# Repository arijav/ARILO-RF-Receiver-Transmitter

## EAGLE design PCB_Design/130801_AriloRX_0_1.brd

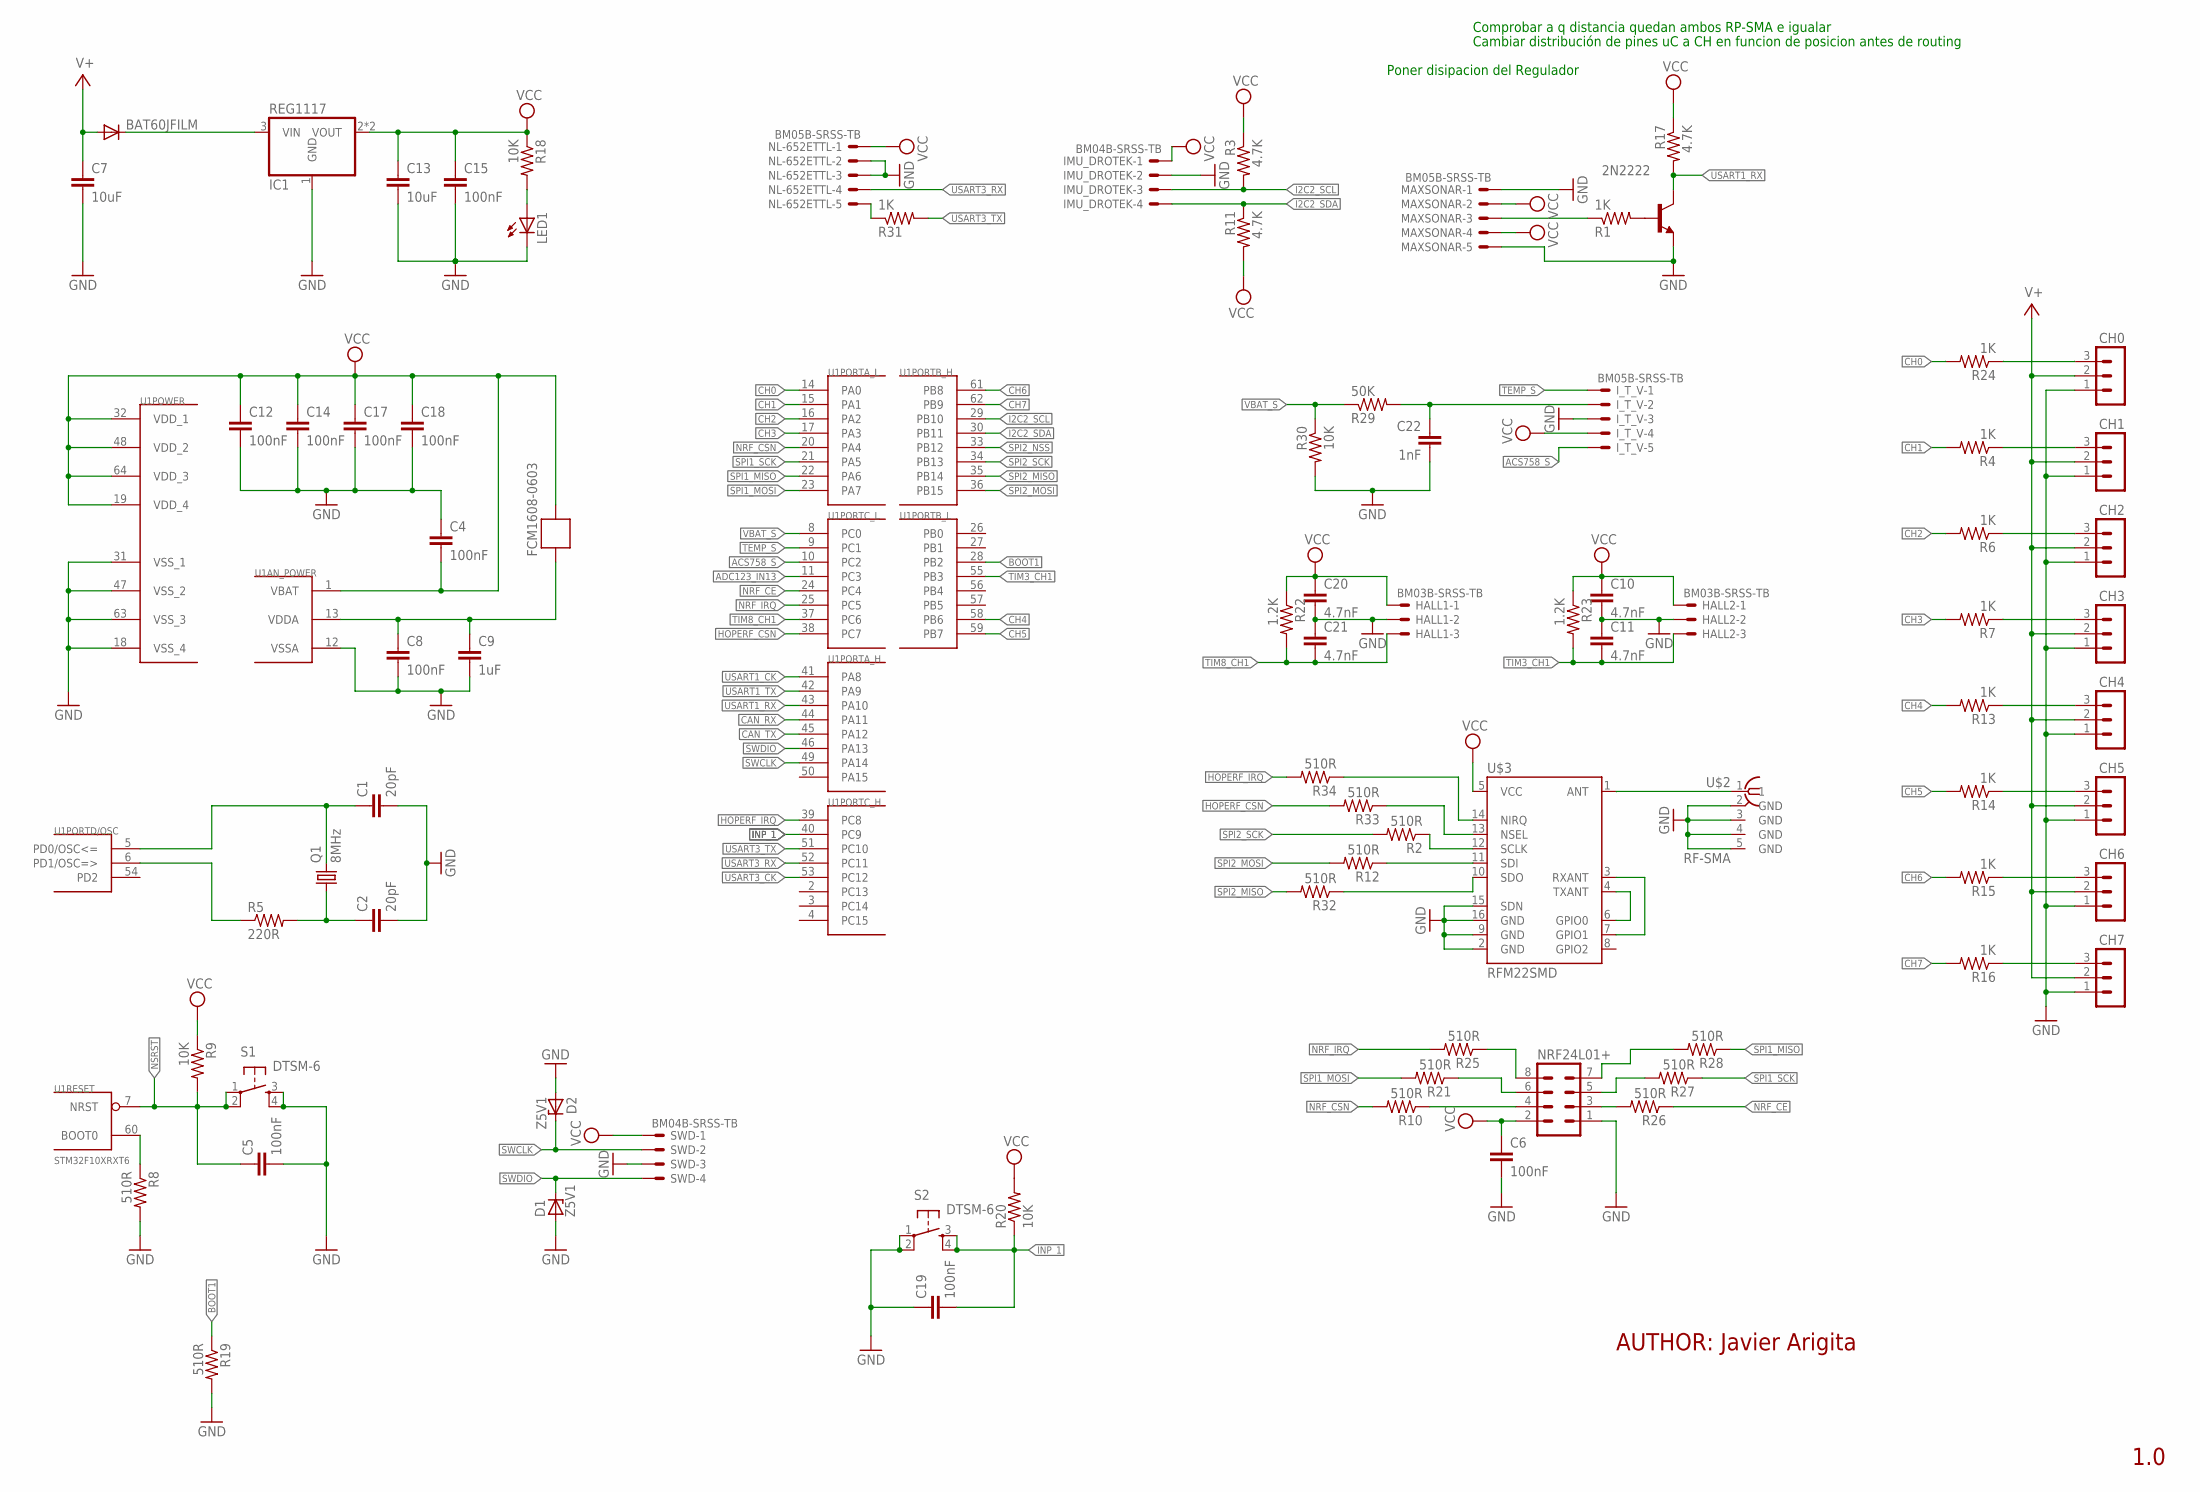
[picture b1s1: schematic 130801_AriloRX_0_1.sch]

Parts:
2N2222: MMBT2222ALT1-NPN-SOT23-BEC; SOT23-BEC
BAT60JFILM: DIODE-SOD323-R; SOD323-R
C1, C2: 20pF; C0805
C4, C5, C6, C8, C12, C14, C15, C17, C18, C19: 100nF; C0805
C7, C13: 10uF; C3216
C9: 1uF; C3216
C10, C11, C20, C21: 4.7nF; C0805
C22: 1nF; C0805
CH0, CH1, CH2, CH3, CH4, CH5, CH6, CH7: MA03-1
D1, D2: Z5V1; SOD80C
FCM1608-0603: FERRITE-BEAD; R0603
HALL1, HALL2: BM03B-SRSS-TB
IC1: REG1117; SOT223
IMU_DROTEK: BM04B-SRSS-TB
I_T_V: BM05B-SRSS-TB
LED1: LED0805; CHIPLED_0805
MAXSONAR: BM05B-SRSS-TB
NL-652ETTL: BM05B-SRSS-TB
NRF24L01+: MA04-2
Q1: 8MHz; SM49
R1, R4, R6, R7, R13, R14, R15, R16, R24, R31: 1K; R0805
R2, R8, R10, R12, R19, R21, R25, R26, R27, R28, R32, R33, R34: 510R; R0805
R3, R11, R17: 4.7K; R0805
R5: 220R; R0805
R9, R18, R20, R30: 10K; R0805
R22, R23: 1.2K; R0805
R29: 50K; R0805
S1, S2: DTSM-6
SWD: BM04B-SRSS-TB
U1: STM32F10XRXT6; TQFP64
U$2: RF-SMA; BU-SMA-H
U$3: RFM22SMD; RFM22-XXX-S2

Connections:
ACS758_S: I_T_V.5, U1.10 (PC2)
ADC123_IN13: U1.11 (PC3)
BOOT1: R19.1, U1.28 (PB2)
CAN_RX: U1.44 (PA11)
CAN_TX: U1.45 (PA12)
CH0: R24.2, U1.14 (PA0)
CH1: R4.2, U1.15 (PA1)
CH2: R6.2, U1.16 (PA2)
CH3: R7.2, U1.17 (PA3)
CH4: R13.2, U1.58 (PB6)
CH5: R14.2, U1.59 (PB7)
CH6: R15.2, U1.61 (PB8)
CH7: R16.2, U1.62 (PB9)
GND: 2N2222.E, C1.2, C2.2, C4.1, C5.2, C6.2, C7.2, C8.2, C9.2, C10.2, C11.1, C12.2, C13.2, C14.2, C15.2, C17.2, C18.2, C19.1, C20.2, C21.1, C22.2, CH0.1, CH1.1, CH2.1, CH3.1, CH4.1, CH5.1, CH6.1, CH7.1, D1.A, D2.A, HALL1.2, HALL2.2, IC1.1 (GND), IMU_DROTEK.2, I_T_V.3, LED1.C, MAXSONAR.1, MAXSONAR.5, NL-652ETTL.2, NL-652ETTL.3, NRF24L01+.1, R8.2, R19.2, R30.2, S1.3, S1.4, S2.1, S2.2, SWD.3, U1.12 (VSSA), U1.18 (VSS_4), U1.31 (VSS_1), U1.47 (VSS_2), U1.63 (VSS_3), U$2.2 (GND), U$2.3 (GND), U$2.4 (GND), U$2.5 (GND), U$3.2 (GND), U$3.9 (GND), U$3.15 (SDN), U$3.16 (GND)
HOPERF_CSN: R33.2, U1.38 (PC7)
HOPERF_IRQ: R34.2, U1.39 (PC8)
I2C2_SCL: IMU_DROTEK.3, R3.2, U1.29 (PB10)
I2C2_SDA: IMU_DROTEK.4, R11.1, U1.30 (PB11)
INP_1: C19.2, R20.1, S2.3, S2.4, U1.40 (PC9)
unnamed: C1.1, Q1.2, U1.5 (PD0/OSC<=)
unnamed: R5.1, U1.6 (PD1/OSC=>)
unnamed: C2.1, Q1.1, R5.2
unnamed: R8.1, U1.60 (BOOT0)
unnamed: U$3.3 (RXANT), U$3.7 (GPIO1)
unnamed: U$3.4 (TXANT), U$3.6 (GPIO0)
unnamed: R2.1, U$3.12 (SCLK)
unnamed: R12.1, U$3.11 (SDI)
unnamed: CH0.3, R24.1
unnamed: LED1.A, R18.2
unnamed: NL-652ETTL.5, R31.1
unnamed: R32.1, U$3.10 (SDO)
unnamed: BAT60JFILM.C, IC1.3 (VIN)
unnamed: MAXSONAR.3, R1.1
unnamed: C22.1, I_T_V.2, R29.2
unnamed: 2N2222.B, R1.2
unnamed: C8.1, C9.1, FCM1608-0603.2, U1.13 (VDDA)
unnamed: NRF24L01+.4, R10.1
unnamed: NRF24L01+.3, R26.2
unnamed: U$2.1, U$3.1 (ANT)
unnamed: CH2.3, R6.1
unnamed: R34.1, U$3.14 (NIRQ)
unnamed: CH4.3, R13.1
unnamed: R33.1, U$3.13 (NSEL)
unnamed: CH3.3, R7.1
unnamed: CH6.3, R15.1
unnamed: CH5.3, R14.1
unnamed: CH7.3, R16.1
unnamed: NRF24L01+.5, R27.2
unnamed: NRF24L01+.6, R21.1
unnamed: NRF24L01+.8, R25.1
unnamed: NRF24L01+.7, R28.2
unnamed: CH1.3, R4.1
NRF_CE: R26.1, U1.24 (PC4)
NRF_CSN: R10.2, U1.20 (PA4)
NRF_IRQ: R25.2, U1.25 (PC5)
NSRST: C5.1, R9.2, S1.1, S1.2, U1.7 (NRST)
SPI1_MISO: R28.1, U1.22 (PA6)
SPI1_MOSI: R21.2, U1.23 (PA7)
SPI1_SCK: R27.1, U1.21 (PA5)
SPI2_MISO: R32.2, U1.35 (PB14)
SPI2_MOSI: R12.2, U1.36 (PB15)
SPI2_NSS: U1.33 (PB12)
SPI2_SCK: R2.2, U1.34 (PB13)
SWCLK: D2.C, SWD.2, U1.49 (PA14)
SWDIO: D1.C, SWD.4, U1.46 (PA13)
TEMP_S: I_T_V.1, U1.9 (PC1)
TIM3_CH1: C11.2, HALL2.3, R23.2, U1.55 (PB3)
TIM8_CH1: C21.2, HALL1.3, R22.2, U1.37 (PC6)
USART1_CK: U1.41 (PA8)
USART1_RX: 2N2222.C, R17.2, U1.43 (PA10)
USART1_TX: U1.42 (PA9)
USART3_CK: U1.53 (PC12)
USART3_RX: NL-652ETTL.4, U1.52 (PC11)
USART3_TX: R31.2, U1.51 (PC10)
V+: BAT60JFILM.A, C7.1, CH0.2, CH1.2, CH2.2, CH3.2, CH4.2, CH5.2, CH6.2, CH7.2
VBAT_S: R29.1, R30.1, U1.8 (PC0)
VCC: C4.2, C6.1, C10.1, C12.1, C13.1, C14.1, C15.1, C17.1, C18.1, C20.1, FCM1608-0603.1, HALL1.1, HALL2.1, IC1.2 (VOUT), IC1.4 (VOUT), IMU_DROTEK.1, I_T_V.4, MAXSONAR.2, MAXSONAR.4, NL-652ETTL.1, NRF24L01+.2, R3.1, R9.1, R11.2, R17.1, R18.1, R20.2, R22.1, R23.1, SWD.1, U1.1 (VBAT), U1.19 (VDD_4), U1.32 (VDD_1), U1.48 (VDD_2), U1.64 (VDD_3), U$3.5 (VCC)

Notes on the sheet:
AUTHOR: Javier Arigita
1.0
Cambiar distribución de pines uC a CH en funcion de posicion antes de routing
Comprobar a q distancia quedan ambos RP-SMA e igualar
Poner disipacion del Regulador

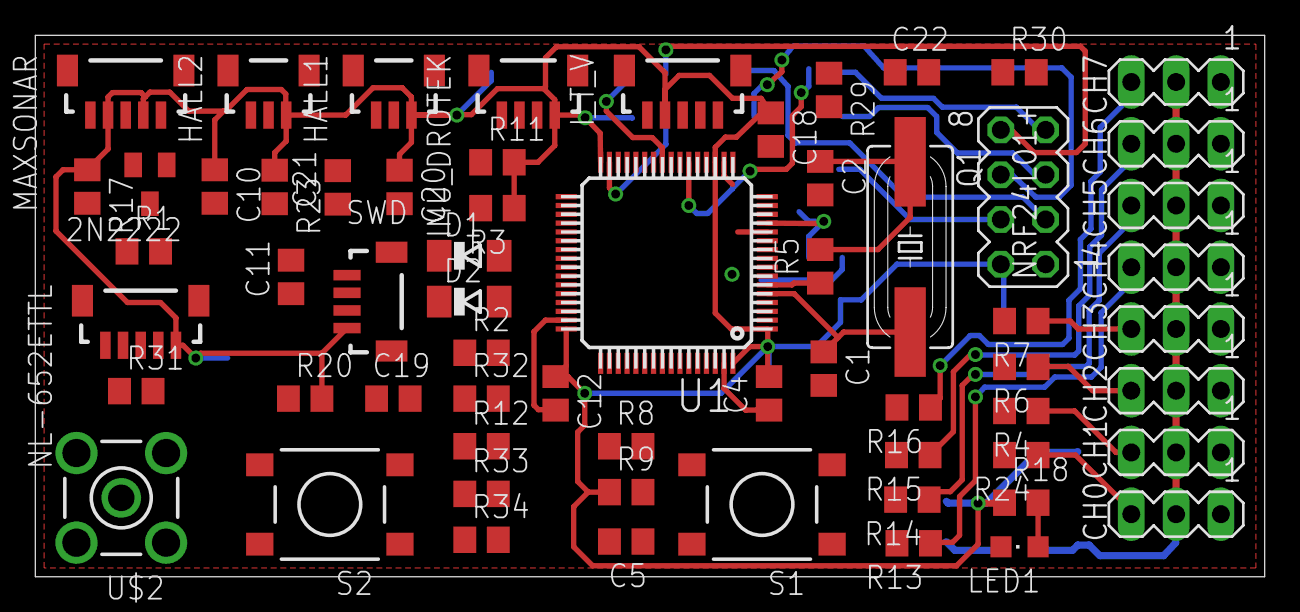
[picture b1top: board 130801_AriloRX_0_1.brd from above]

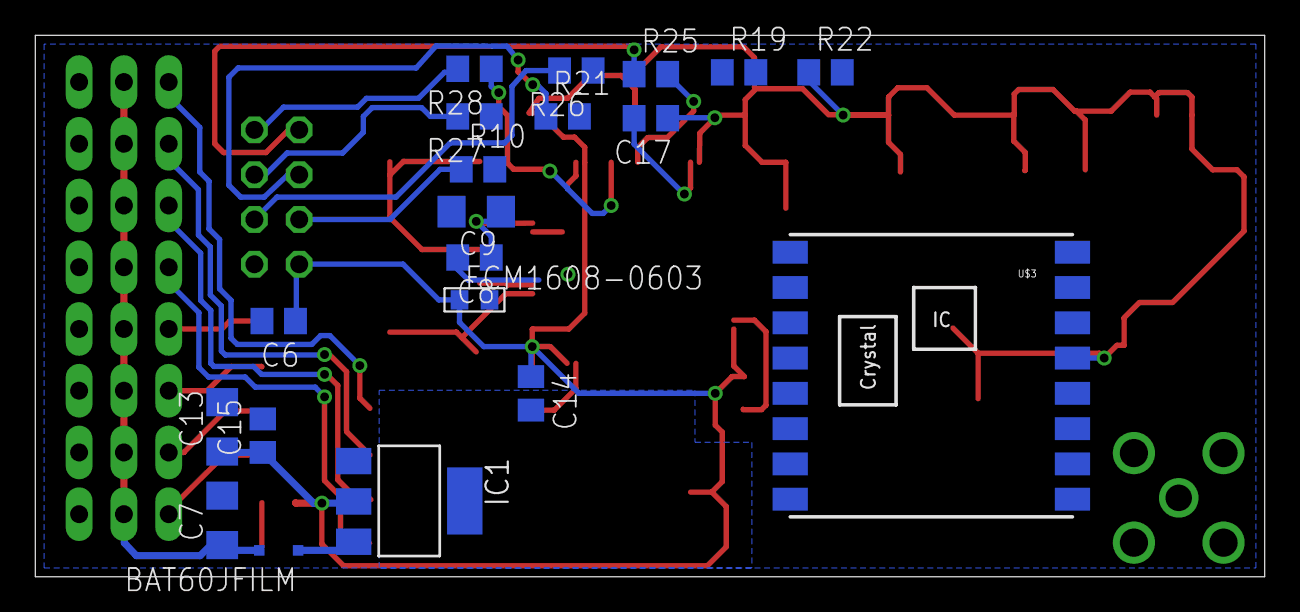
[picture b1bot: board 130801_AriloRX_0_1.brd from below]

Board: 2 copper layers, 69.7 x 30.7 mm, 83 parts (20 on the bottom side), 70 nets.

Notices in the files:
parts and their libraries:
SparkFun-RF: Licensing: CC v3.0 Share-Alike You are welcome to use this library for commercial purposes.
